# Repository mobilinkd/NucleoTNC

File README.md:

# NucleoTNC Firmware

Source code for STM32L432KC Nucleo32-based TNC (PCB & breadboard version).

http://www.mobilinkd.com/2019/06/24/nucleotnc/

# Building the Firmware

Use Eclipse with CDT and the GNU MCU Eclipse plugins.

If you are porting this to another build platform, you will need to
build the firmware using the same compiler and linker options.  As
with most firmware projects, there is a linker script with defines
the memory layout for for the Flash and SRAM.

## Blaze Dependency

There is a new dependency as of 2.4.3 with the addition of the Kalman
filter.  The firmware has a dependency on the Blaze C++ math library.

    mkdir blaze
    ln -s /usr/include/blaze blaze/

This also requires (for now) that the firmware be built with exceptions
enabled.

## Example GCC Command-line

Below are example compilation and linking lines for reference:

    arm-none-eabi-g++ -mcpu=cortex-m4 -mthumb -mfloat-abi=softfp -mfpu=fpv4-sp-d16 -O2 -fmessage-length=0 -fsigned-char -ffunction-sections -fdata-sections -fno-inline-functions -fsingle-precision-constant -fstack-usage -fstrict-aliasing -ffast-math -Wall -Wextra -Wlogical-op -Wfloat-equal -g -D__FPU_PRESENT=1 -DUSE_HAL_DRIVER -DARM_MATH_CM4 -DSTM32L432xx -D__weak=__attribute__((weak)) -DNUCLEOTNC=1 -I../Inc -I../Drivers/STM32L4xx_HAL_Driver/Inc -I/home/rob/workspace/Nucleo_L432KC_TNC/Inc -I/home/rob/workspace/Nucleo_L432KC_TNC/Drivers/STM32L4xx_HAL_Driver/Inc -I/home/rob/workspace/Nucleo_L432KC_TNC/Drivers/CMSIS/Include -I/home/rob/workspace/Nucleo_L432KC_TNC/Drivers/CMSIS/Device/ST/STM32L4xx/Include -I/home/rob/workspace/Nucleo_L432KC_TNC/Middlewares/Third_Party/FreeRTOS/Source/include -I/home/rob/workspace/Nucleo_L432KC_TNC/Middlewares/Third_Party/FreeRTOS/Source/CMSIS_RTOS -I/home/rob/workspace/Nucleo_L432KC_TNC/Middlewares/Third_Party/FreeRTOS/Source/portable/GCC/ARM_CM4F -I/home/rob/workspace/Nucleo_L432KC_TNC/TNC -I/usr/arm-none-eabi/include -std=gnu++1z -fabi-version=9 -fno-exceptions -fno-rtti -fno-use-cxa-atexit -fno-threadsafe-statics -Wno-register -c -o TNC/HdlcFrame.o ../TNC/HdlcFrame.cpp 
    arm-none-eabi-g++ -mcpu=cortex-m4 -mthumb -mfloat-abi=softfp -mfpu=fpv4-sp-d16 -O2 -fmessage-length=0 -fsigned-char -ffunction-sections -fdata-sections -fno-inline-functions -fsingle-precision-constant -fstack-usage -fstrict-aliasing -ffast-math -Wall -Wextra -Wlogical-op -Wfloat-equal -g -T /home/rob/workspace/Nucleo_L432KC_TNC/STM32L432KC_FLASH.ld -Xlinker --gc-sections -Wl,-Map,firmware.map --specs=nano.specs -o firmware.elf Drivers/STM32L4xx_HAL_Driver/Src/stm32l4xx_hal.o Drivers/STM32L4xx_HAL_Driver/Src/stm32l4xx_hal_adc.o Drivers/STM32L4xx_HAL_Driver/Src/stm32l4xx_hal_adc_ex.o Drivers/STM32L4xx_HAL_Driver/Src/stm32l4xx_hal_cortex.o Drivers/STM32L4xx_HAL_Driver/Src/stm32l4xx_hal_crc.o Drivers/STM32L4xx_HAL_Driver/Src/stm32l4xx_hal_crc_ex.o Drivers/STM32L4xx_HAL_Driver/Src/stm32l4xx_hal_dac.o Drivers/STM32L4xx_HAL_Driver/Src/stm32l4xx_hal_dac_ex.o Drivers/STM32L4xx_HAL_Driver/Src/stm32l4xx_hal_dma.o Drivers/STM32L4xx_HAL_Driver/Src/stm32l4xx_hal_dma_ex.o Drivers/STM32L4xx_HAL_Driver/Src/stm32l4xx_hal_flash.o Drivers/STM32L4xx_HAL_Driver/Src/stm32l4xx_hal_flash_ex.o Drivers/STM32L4xx_HAL_Driver/Src/stm32l4xx_hal_flash_ramfunc.o Drivers/STM32L4xx_HAL_Driver/Src/stm32l4xx_hal_gpio.o Drivers/STM32L4xx_HAL_Driver/Src/stm32l4xx_hal_i2c.o Drivers/STM32L4xx_HAL_Driver/Src/stm32l4xx_hal_i2c_ex.o Drivers/STM32L4xx_HAL_Driver/Src/stm32l4xx_hal_opamp.o Drivers/STM32L4xx_HAL_Driver/Src/stm32l4xx_hal_opamp_ex.o Drivers/STM32L4xx_HAL_Driver/Src/stm32l4xx_hal_pwr.o Drivers/STM32L4xx_HAL_Driver/Src/stm32l4xx_hal_pwr_ex.o Drivers/STM32L4xx_HAL_Driver/Src/stm32l4xx_hal_rcc.o Drivers/STM32L4xx_HAL_Driver/Src/stm32l4xx_hal_rcc_ex.o Drivers/STM32L4xx_HAL_Driver/Src/stm32l4xx_hal_rng.o Drivers/STM32L4xx_HAL_Driver/Src/stm32l4xx_hal_rtc.o Drivers/STM32L4xx_HAL_Driver/Src/stm32l4xx_hal_rtc_ex.o Drivers/STM32L4xx_HAL_Driver/Src/stm32l4xx_hal_tim.o Drivers/STM32L4xx_HAL_Driver/Src/stm32l4xx_hal_tim_ex.o Drivers/STM32L4xx_HAL_Driver/Src/stm32l4xx_hal_uart.o Drivers/STM32L4xx_HAL_Driver/Src/stm32l4xx_hal_uart_ex.o Middlewares/Third_Party/FreeRTOS/Source/CMSIS_RTOS/cmsis_os.o Middlewares/Third_Party/FreeRTOS/Source/croutine.o Middlewares/Third_Party/FreeRTOS/Source/event_groups.o Middlewares/Third_Party/FreeRTOS/Source/list.o Middlewares/Third_Party/FreeRTOS/Source/portable/GCC/ARM_CM4F/port.o Middlewares/Third_Party/FreeRTOS/Source/portable/MemMang/heap_4.o Middlewares/Third_Party/FreeRTOS/Source/queue.o Middlewares/Third_Party/FreeRTOS/Source/tasks.o Middlewares/Third_Party/FreeRTOS/Source/timers.o Src/arm_fir_f32.o Src/arm_fir_fast_q15.o Src/arm_fir_init_f32.o Src/arm_fir_init_q15.o Src/arm_fir_interpolate_init_q15.o Src/arm_fir_interpolate_q15.o Src/arm_offset_q15.o Src/arm_q15_to_float.o Src/freertos.o Src/main.o Src/stm32l4xx_hal_msp.o Src/stm32l4xx_hal_timebase_TIM.o Src/stm32l4xx_it.o Src/system_stm32l4xx.o TNC/AFSKModulator.o TNC/AFSKTestTone.o TNC/Afsk1200Demodulator.o TNC/AfskDemodulator.o TNC/AudioInput.o TNC/AudioLevel.o TNC/DCD.o TNC/Demodulator.o TNC/FilterCoefficients.o TNC/Fsk9600Demodulator.o TNC/Fsk9600Modulator.o TNC/Goertzel.o TNC/Golay24.o TNC/HdlcDecoder.o TNC/HdlcFrame.o TNC/IOEventTask.o TNC/Kiss.o TNC/KissHardware.o TNC/KissTask.o TNC/LEDIndicator.o TNC/Log.o TNC/M17.o TNC/M17Demodulator.o TNC/M17Encoder.o TNC/M17Modulator.o TNC/ModulatorTask.o TNC/NullPort.o TNC/PortInterface.o TNC/SerialPort.o newlib/_exit.o newlib/_sbrk.o newlib/_syscalls.o startup/startup_stm32l432xx.o 

All of the macros defined on the compiler line are important in order
to properly build the firmware.

# Installing firmware

Firmware can be installed via the storage interface (drag & drop), the
on-board ST/LINK port, or via USB DFU.

## Drag & Drop

For the NucleoTNC, the easiest way to install firmware is to copy the
firmware file to the TNC directly.  The NucleoTNC will show up as a storage
device when plugged in.  Just copy the firmware.bin file into the shared
folder.  The firmware will automatically install, the NucleoTNC will reset,
and the new firmware will be running.

## ST/Link

The ST/Link port is a debug port exposed by the NucleoTNC.  It can be used
by Eclipse and other IDEs to directly upload the firmware to the TNC.

## USB DFU

 1. Download the STM32CubeProgrammer.
    https://s3.amazonaws.com/mobilinkd/en.stm32cubeprog-1.4.0.zip
    This programmer will work on Linux, OS X, and Windows.

 2. Download the ELF file from the release (or that you have built from source).

 3. Run the STM32CubeProgrammer from the command-line. (Replace "firmware.elf" with the appropriate firmware filename.)

    ./STM32_Programmer_CLI -c port=USB1 -d firmware.elf -v -g 0x8000000

 4. When that is complete, the NucleoTNC will restart with the new firmware.

----

## Important Note
If you regenerate the STM32 code, please note that the LL ADC driver in
the 1.12.0 version of the HAL driver is buggy.

   Drivers/STM32L4xx_HAL_Driver/Inc/stm32l4xx_ll_adc.h

This file has been modified to address the defect.  If it is replaced by
STM32CubeMX, please ensure that the defect has been fixed.

Details of the defect are available [on the ST community site](https://community.st.com/s/question/0D50X00009bLP0eSAG/adc-init-bug-with-optimization-o1-stm32l4 ADC init bug with optimization >= -O1).

----

## TNC Build Instructions

Please go here: [TNC Build Instructions](Build/NucleoTNC.ipynb)

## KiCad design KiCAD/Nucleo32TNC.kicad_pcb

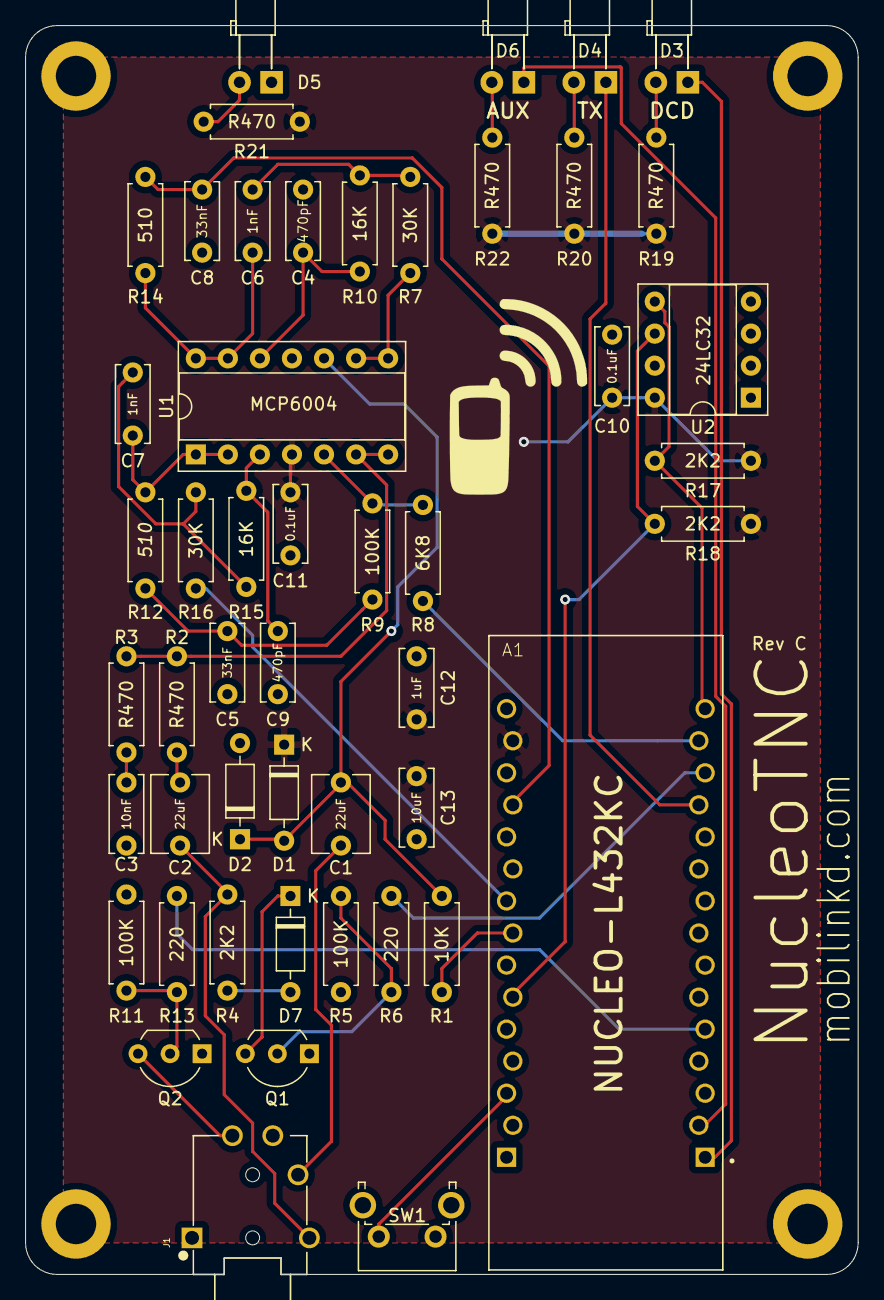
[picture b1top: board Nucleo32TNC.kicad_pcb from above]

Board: 2 copper layers, 66.0 x 99.0 mm, 54 parts (0 on the bottom side), 38 nets.

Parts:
A1: NUCLEO-L432KC; MODULE_NUCLEO-L432KC
C1, C2: 22uF; C_Disc_D6.0mm_W4.4mm_P5.00mm
C3: 10nF; C_Disc_D6.0mm_W2.5mm_P5.00mm
C4, C9: 470pF; C_Disc_D6.0mm_W2.5mm_P5.00mm
C5, C8: 33nF; C_Disc_D6.0mm_W2.5mm_P5.00mm
C6, C7: 1nF; C_Disc_D6.0mm_W2.5mm_P5.00mm
C10, C11: 0.1uF; C_Disc_D6.0mm_W2.5mm_P5.00mm
C12: 1uF; C_Disc_D6.0mm_W2.5mm_P5.00mm
C13: 10uF; C_Disc_D6.0mm_W2.5mm_P5.00mm
D1, D2, D7: BAT85; D_DO-35_SOD27_P7.62mm_Horizontal
D3: GRN LED; LED_D3.0mm_Horizontal_O3.81mm_Z2.0mm
D4: RED LED; LED_D3.0mm_Horizontal_O3.81mm_Z2.0mm
D5: BLU LED; LED_D3.0mm_Horizontal_O3.81mm_Z2.0mm
D6: YEL LED; LED_D3.0mm_Horizontal_O3.81mm_Z2.0mm
G1: LOGO
H1, H2, H3, H4: MountingHole_Pad; MountingHole_3.2mm_M3_ISO14580_Pad
J1: AudioJack4; CUI_SJ-43515TS
Q1, Q2: 2N7000; TO-92_Inline_Wide
R1: 10K; R_Axial_DIN0207_L6.3mm_D2.5mm_P7.62mm_Horizontal
R2, R3, R19, R20, R21, R22: R470; R_Axial_DIN0207_L6.3mm_D2.5mm_P7.62mm_Horizontal
R4, R17, R18: 2K2; R_Axial_DIN0207_L6.3mm_D2.5mm_P7.62mm_Horizontal
R5, R9, R11: 100K; R_Axial_DIN0207_L6.3mm_D2.5mm_P7.62mm_Horizontal
R6, R13: 220; R_Axial_DIN0207_L6.3mm_D2.5mm_P7.62mm_Horizontal
R7, R16: 30K; R_Axial_DIN0207_L6.3mm_D2.5mm_P7.62mm_Horizontal
R8: 6K8; R_Axial_DIN0207_L6.3mm_D2.5mm_P7.62mm_Horizontal
R10, R15: 16K; R_Axial_DIN0207_L6.3mm_D2.5mm_P7.62mm_Horizontal
R12, R14: 510; R_Axial_DIN0207_L6.3mm_D2.5mm_P7.62mm_Horizontal
SW1: SW_Push; SW_Tactile_SPST_Angled_PTS645Vx58-2LFS
U1: MCP6004; DIP-14_W7.62mm_Socket
U2: 24LC32; DIP-8_W7.62mm_Socket

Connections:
+3V3: A1.4.14, C10.1, C11.1, C12.1, C13.1, D1.1, R17.1, R18.1, R19.1, R20.1, R21.1, R22.1, U1.4, U2.8
/ADC_AUDIO: A1.4.12, C8.2, R14.1
/AUDIO_ATTEN: A1.3.14, R8.2
/AUDIO_IN: C1.2, J1.T
/AUDIO_OUT: C2.1, J1.R2, R4.2
/DAC_AUDIO: A1.4.9, R16.2
/DC_OFFSET: A1.4.8, R1.2
/I2C_SCL: A1.4.6, R18.2, U2.6
/I2C_SDA: A1.3.15, R17.2, U2.5
/LED_DCD: A1.3.1, D3.1
/LED_MISC: A1.3.2, D6.1
/LED_TX: A1.3.12, D4.1
/PTT: J1.R1, Q2.3
/PTT_MULTIPLEX: A1.3.13, R6.1
/PTT_SIMPLEX: A1.3.5, R13.1
GND: A1.3.4, A1.4.2, C3.1, C4.1, C5.1, C8.1, C9.1, C10.2, C11.2, C12.2, C13.2, D2.2, D5.1, H1.1, H2.1, H3.1, H4.1, J1.S, Q1.1, Q2.1, R5.2, R11.2, SW1.1, U1.11, U2.1, U2.2, U2.3, U2.4, U2.7
unnamed: A1.4.3, SW1.2
unnamed: C1.1, D1.2, D2.1, R1.1, U1.10
unnamed: C2.2, R2.2
unnamed: C3.2, R3.2
unnamed: C4.2, R10.1, U1.12
unnamed: C5.2, R9.1, R12.2
unnamed: C6.1, R14.2, U1.13, U1.14
unnamed: C6.2, R7.1, R10.2
unnamed: C7.1, R15.1, R16.1
unnamed: C7.2, R12.1, U1.1, U1.2
unnamed: C9.2, R15.2, U1.3
unnamed: D3.2, R19.2
unnamed: D4.2, R20.2
unnamed: D5.2, R21.2
unnamed: D6.2, R22.2
unnamed: D7.1, Q1.3
unnamed: D7.2, R4.1
unnamed: Q1.2, R5.1, R6.2
unnamed: Q2.2, R11.1, R13.2
unnamed: R2.1, R3.1, U1.6, U1.7
unnamed: R7.2, U1.8, U1.9
unnamed: R8.1, R9.2, U1.5

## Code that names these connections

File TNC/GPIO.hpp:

// Copyright 2017 Mobilinkd LLC <rob@mobilinkd.com>
// All rights reserved.

#ifndef MOBILINKD__TNC__GPIO_HPP_
#define MOBILINKD__TNC__GPIO_HPP_

#include "main.h"
#include "stm32l4xx_hal.h"
#include <cstdint>

namespace mobilinkd { namespace tnc {

template <uint32_t BANK, uint16_t PIN>
struct GPIO {
    static void on() {
        HAL_GPIO_WritePin(reinterpret_cast<GPIO_TypeDef*>(BANK), PIN, GPIO_PIN_SET);
    }
    static void off() {
        HAL_GPIO_WritePin(reinterpret_cast<GPIO_TypeDef*>(BANK), PIN, GPIO_PIN_RESET);
    }
    static void toggle() {
        HAL_GPIO_TogglePin(reinterpret_cast<GPIO_TypeDef*>(BANK), PIN);
    }
    static bool get() {
        return HAL_GPIO_ReadPin(reinterpret_cast<GPIO_TypeDef*>(BANK), PIN);
    }
#if 0
    static bool operator bool() {
        return HAL_GPIO_ReadPin(BANK, PIN);
    }
    static bool operator=(bool value) {
        return HAL_GPIO_WritePin(BANK, PIN, GPIO_PinState(value));
    }
#endif
};

namespace gpio {

typedef GPIO<(uint32_t)GPIOA_BASE,PTT_S_Pin> PTT_SIMPLEX;
typedef GPIO<(uint32_t)GPIOA_BASE,PTT_M_Pin> PTT_MULTIPLEX;
typedef GPIO<(uint32_t)GPIOA_BASE,LED_RED_Pin> LED_TX;
typedef GPIO<(uint32_t)GPIOA_BASE,LED_GREEN_Pin> LED_DCD;
typedef GPIO<(uint32_t)GPIOA_BASE,LED_YELLOW_Pin> LED_OTHER;
typedef GPIO<(uint32_t)GPIOB_BASE,AUDIO_OUT_ATTEN_Pin> AUDIO_OUT_ATTEN;
typedef GPIO<(uint32_t)GPIOB_BASE,LD3_Pin> LD3;

}}} // mobilinkd::tnc::gpio

#endif // MOBILINKD__TNC__GPIO_HPP_

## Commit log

2018-07-29 Initial STM32CubeMX code generation.
2018-07-29 Add support for using SRAM2 separate from SRAM1.
2018-07-30 Add TNC code, openocd configs, etc.
2018-08-06 Use tickless idle, and add stack overflow detection.
2018-08-06 Move some pins around, use LED3, and name the AUDIO_IN pin. Initialize DAC, Op Amp and ADC in main(). Increase ADC clock to 80MHz and enable 16x oversampling. Increase sample time to 6.5 cycles. Supp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
2018-08-06 Remove extraneous logging.
2018-08-06 Make it save to use LEDs in ISR.
2018-08-06 Use KISS-based logging since SWO does not work on Nucleo32.
2018-08-06 Fix defect in L4 HAL version 1.12.0 LL ADC code that misconfigures the ADC channel.
2018-08-06 Fix & enable I2C EEPROM support.
2018-08-11 Fix DAC output glitch when starting transmission.
2018-08-11 Support setting/getting MYCALL. Add new modem types.
2018-08-12 Fix broken critical section handling when toggling LEDs.
2018-08-14 Cannot use TRACESWO on Nucleo32 boards.
2018-08-14 Add note about fixing ADC LL driver to README.
2019-02-12 Update README.md
    Start adding build instructions.
2019-06-23 Massive update to get the NucleoTNC firmware up to date with the TNC3. Mostly improvements to the moduleator and demodulator sections. Fix EEPROM read/write. Update version number to 1.0.0.
2019-06-23 Add KiCAD files and build instructions.
2019-06-23 Updates to the build instructions, including programming, configuration and troubleshooting.
2019-06-24 Fix a missing build step. Add a configuration step (Save Settings). Add more diagnostics and troubleshooting steps.
2019-06-24 Schematic not displaying.
2019-06-24 Add missing image file. Fix some formatting issues, spelling and awkward wording.
2019-06-25 Update notebook links to point to nbviewer.
2020-01-07 Add harware init mutex.
2020-01-07 Increase clock speed to 80MHz and disable ADC oversampling.
2020-01-07 Fix SLIP encoding defect in frame encoder.
2020-01-08 Don't init PTT during EEPROM init.
2020-01-08 Wait, don't crash, when a buffer is unavailable.
2020-01-08 Release hardware init mutex only after EEPROM settings are available.
2020-01-08 Update version to 1.0.1. Fix null pointer deref. Respond properly to SAVE_EEPROM command.
2020-01-10 Start of 9600 baud support.
2020-03-16 Add new 60mm PCB.
2020-03-16 Save PCB with KiCAD 5.1.5 (stable).
2020-05-06 Rev B of 67mm board. Fix logo, move blue LED a bit, update C1 value, and expand Nucleo pin offsets for press-fit. Fix hole locations and significant alignment issues in front and rear panels. Change 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
2020-05-06 Update the rev on the pcb notes. Remove backup files. Update .gitignore for KiCAD files.
2020-05-06 Remove unneeded ZIP files.
2020-05-06 Update schematic C1 and add dimensions for mounting holes to PCB.
2020-05-08 Add fabrication notes to indicate where to place production codes.
2020-05-29 Add NucleoTNC Rev B PCB, spacer and enclosure panels.
2020-05-29 Add some docs.
2020-06-01 Update footprints in schematic, and values for J1 and SW1 in schematic and PCB. Add an interactive BOM. Update the README.
2020-06-01 Update links in README.
2020-12-07 Add gerbers.
2020-12-07 Update 9600 baud code.
2021-01-03 Add M17 support. Refactor code so it is much closer to TNC3 codebase.
2021-01-03 More TNC3 codebase alignment.
2021-01-03 Update documentation and make one small part change to improve 9600 baud and M17 decode performance.
2021-01-03 Remove temp file and update gitignore.
2021-01-03 Fix incorrect C2 designator for audio input section (should be C1).
2021-01-04 Fix some copy/paste issues with the README to address NucleoTNC-specific behavior.
2021-01-23 Move demodulator control from encoder to modulator. Fix stream encoding. Improve stream buffering.
2021-01-23 Adjust clock recovery timing constraints for improved demodulation.
2021-01-23 Increase logging priority of modulator enable/disable.
2021-01-23 Bump firmware version to 2.1.5.
2021-02-22 Sync NucleoTNC firmware with TNC3 v2.1.8 codebase. Upgrade compiler to GCC 10.2. Upgrade to C++20 for std::span. Changes to reduce stack utilization. Reduce jitter by adjusting clocks & interrupt pri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
2021-06-20 Statically allocate buffers needed for serial thread and queue. Limit frame churn.
2021-06-21 Make FIR filter input and output buffers global to reduce RAM consumption.
2021-06-21 Update callsign decoding based on spec clarification.
2021-06-21 Add TNC_DEBUG macro because STMCubeIDE defines DEBUG macro.
2021-06-21 Add missing include files.
2021-06-21 Fix memory leak (frame buffers) in M17 packet handling.
2021-06-21 Add new components for updated M17 demodulator.
2021-06-21 Update M17 modulator to use 72MHz clock for increased accuracy.
2021-06-21 Major change to M17 demodulator. Improves demod performance, perhaps at the expense of tracking signals with extremely inaccurate clocks. It should be able to handle up to ~500ppm error between TX & 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
2021-06-21 Remove now-unused M17 components.
2021-06-21 Add missing function declaration for SysClock72().
2021-06-22 Fix empty body warning when not logging.
2021-06-22 Revert NucleoTNC log level change.
2021-06-22 Update clock trees. Update 1200 baud modem to run at 48MHz, same as TNC3. Update 9600 baud modem to run at 72MHz instead of 80MHz. Fixes 9600 baud mode broken by M17 changes.
2021-06-22 Update version to 2.2.2.
2021-06-22 Update 1200 baud modem to use same timing on both TNC3 and NucleoTNC.
2021-06-22 Fix peripheral clock tree.
2021-06-23 Simplify & correct clock trees.
2021-06-23 Enable oversampling for all demodulators.
2021-06-26 Set I2C timing to 400kHz for EEPROM access.
2021-06-26 Use same Viterbi code as m17-cxx-demod.
2021-06-26 Share storage for all demodulators.
2021-07-01 Simplify FIR filter code.
2021-07-01 Update firmware to use new stream frame format. Update version to 2.3.0.
2021-07-09 Add support for frame resizing. Handle old stream frame type in encoder.
2021-07-09 Add missing includes.
2021-07-17 Update comment.
2021-07-17 Update C++ ABI and compiler version.
2021-07-17 Changes to clock tree to better support frequency changes.
2021-07-17 Add Schottky diode on AUDIO OUT to eliminate the DC bias caused by Q1 body diode and C2.
2021-07-17 Use wide footprint for Q1 and Q2 to help with hand soldering.
2021-07-18 Update C1 & C2 values to 22uF and footprint size. Update decoupling capacitor footprints.
2021-07-18 Use larger footprints for C12 and C13.
2021-07-18 Update to Rev C.
2021-07-18 Update PCB to Rev C. Larger footprints for C1, C2, C10, C11, C12, C13, Q1, & Q2. Add new diode D7.
2021-07-18 Fix a small silkscreen error. Move part designators for op amp, EEPROM and Nucleo board to silkscreen.
2021-08-04 Add support for BER testing. Update version to v2.3.2
2021-08-30 New LSF puncture matrix (P1).
2021-08-30 Update EOS check.
2021-08-30 Update to version 2.3.3.
2021-09-06 Add new EOT indicator. Send RSSI/cost info for stream data. Update version to 2.4.0.
2021-10-26 Fix M17 RX reverse polarity.
2022-01-23 The FirFilter constructor and init function do not need to be templatized.
2022-01-23 Trivial optimization to Viterbi.
2022-01-23 Validate the LICH fragment number and mask the LICH segment bitfield properly. Send -1 for BER while LICH decode is incomplete.
2022-01-23 Add 8 and 11 symbol RRC filters to M17 demod.
2022-01-23 Update FT-991 setup.
2022-01-23 Add M17 Setup Guide.
2022-01-23 Small update to docs.
2022-01-23 Update firmware version to 2.4.2.
2022-01-23 Add reset() function to IIR filter.
2022-01-23 Use an 8-symbol length FIR filter for symbol interpolation.
2022-01-23 Add feature to allow forced DCD unlocking to aid in modem recycling.
2022-01-23 Allow more time for DC offset to settle.
2022-01-23 Add Kalman filter code. This adds a dependency on Blaze and requires that exceptions be enabled.
2022-01-23 Add symbol slope integrator code (currently unused).
2022-01-23 Use EOT sync word for end of stream rather than EOS bit. Use only sync word and Kalman filter for clock recovery. Simplify some of the state transistions. Reduce DCD limits since we can follow symbol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
2022-01-23 Add missing include.
2022-01-23 Update FT-991 config.
2022-01-23 Change clock used for M17 to 48MHz.
2022-01-23 Update firmware version to 2.4.3.
2022-01-23 Make the adcInputQueue size match the number of buffers allocated in AudioInput.hpp (8).
2022-01-23 Update README.md for Blaze dependency.
2022-02-20 Add BOM for rev C PCB.
2022-05-29 Update to version 2.4.4. Clock recovery improvements. Update the sample index more frequently to reduce EVM. Re-wrote the symbol deviation, offset, EVM code. More code comments.
2023-07-23 Fix typos in NucleoTNC.ipynb
